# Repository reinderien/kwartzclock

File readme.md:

This is the code associated with the
[KwartzLab electronics demo event](https://gist.github.com/reinderien/ab7dbbdbca7b7f1a77dfda12d686f1ef).

Also see the
[bill of materials](https://docs.google.com/spreadsheets/d/1yXx0iprRUhsX16thSTnNfLWV875vi7FYF72Nl2V39cM/edit?usp=sharing).

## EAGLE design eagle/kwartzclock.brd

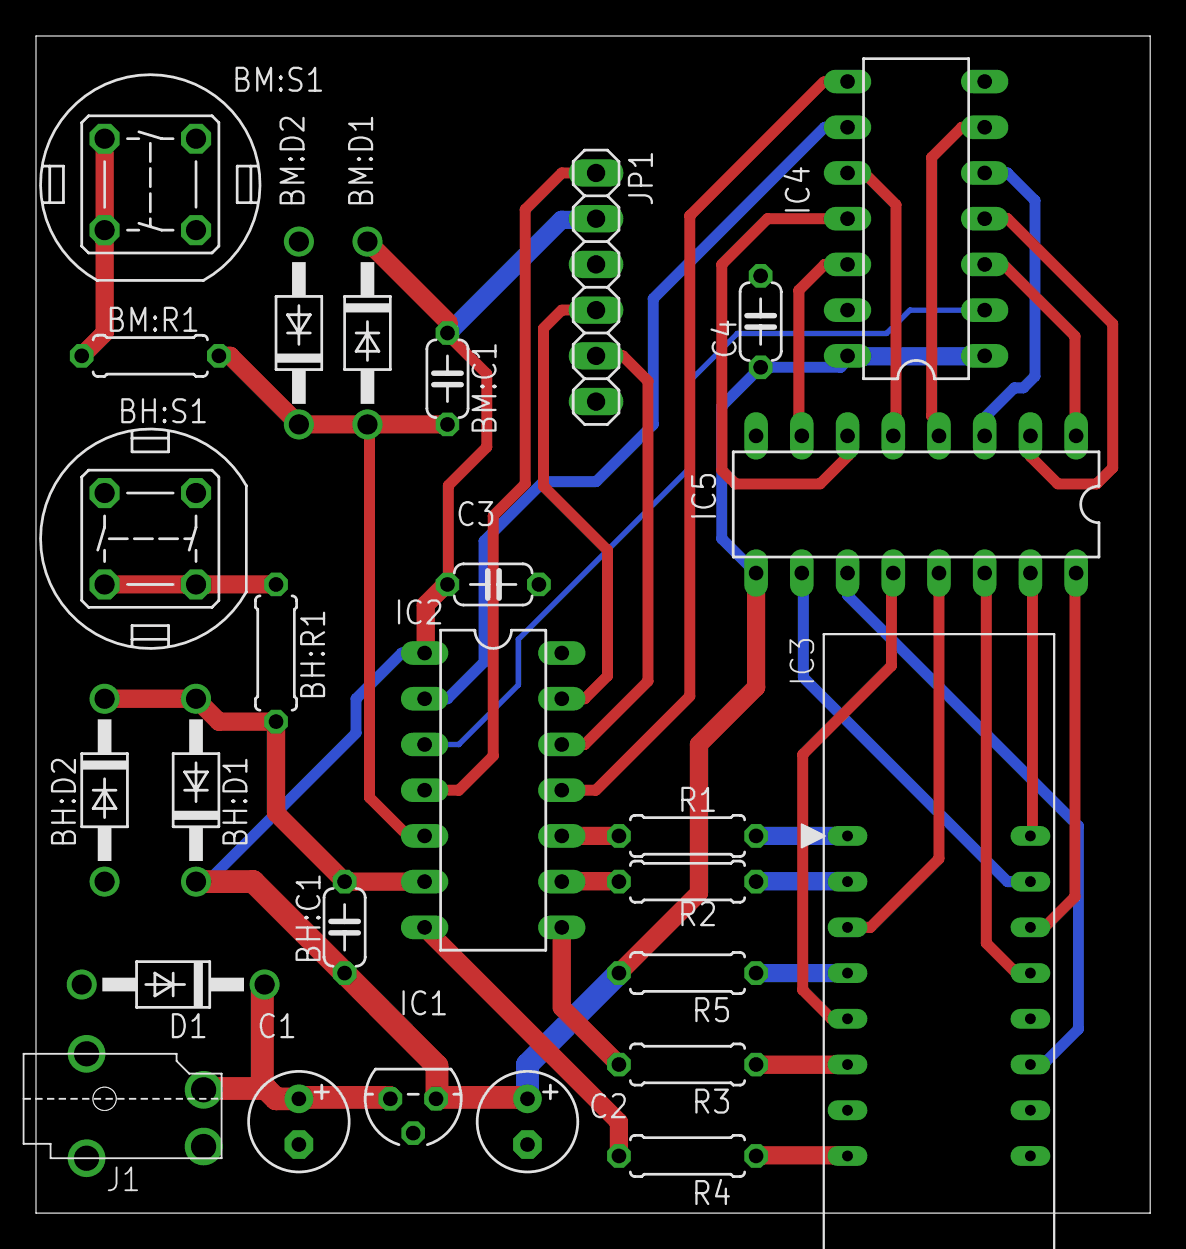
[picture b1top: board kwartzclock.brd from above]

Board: 2 copper layers, 61.9 x 65.4 mm, 27 parts (0 on the bottom side), 36 nets.

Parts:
BH:C1: 330nF; C050-024X044
BH:D1, BH:D2: SB160; DO41-10
BH:R1: 470R; 0207/7
BH:S1: TR1-01; DTE6
BM:C1: 330nF; C050-024X044
BM:D1, BM:D2: SB160; DO41-10
BM:R1: 470R; 0207/7
BM:S1: TR1-01; DTE6
C1, C2: 10uF; E2,5-6
C3, C4: 2.2uF; C050-024X044
D1: SB160; DO41-10
IC1: L78L33ACZ; TO92
IC2: PIC18(L)F15323-I/P; DIL14
IC3: TGCG1050M; DIP16-WIDE
IC4: 74HC164N; DIL14
IC5: ULN2003AN; DIL16
J1: PJ-071
JP1: PH1-06-UA; 1X06
R1, R2, R3, R4: 91R; 0207/7
R5: 330R; 0207/7

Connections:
!CLR: IC2.2, IC4.9
!DRVA: IC3.14, IC5.16
!DRVB: IC3.16, IC5.15
!DRVC: IC3.13, IC5.14
!DRVD: IC3.3, IC5.13
!DRVE: IC3.5, IC5.12
!DRVF: IC3.11, IC5.11
!DRVG: IC3.15, IC5.10
!HBUT: BH:C1.2, BH:D1.A, BH:D2.C, BH:R1.2, IC2.6
!MBUT: BM:C1.2, BM:D1.A, BM:D2.C, BM:R1.2, IC2.5
!MCLR: IC2.4, JP1.1
+3V3: BH:C1.1, BH:D1.C, BM:C1.1, BM:D1.C, C2.+, C3.1, C4.1, IC1.1, IC2.1, IC4.1, IC4.14, IC5.9, JP1.2, R5.2
BH:!BUT_IN: BH:R1.1, BH:S1.1, BH:S1.2
BM:!BUT_IN: BM:R1.1, BM:S1.1, BM:S1.2
CLK: IC2.11, IC4.8
D1: IC2.10, R1.2
D1LIM: IC3.1, R1.1
D2: IC2.9, R2.2
D2LIM: IC3.2, R2.1
D3: IC2.8, R3.2
D3LIM: IC3.6, R3.1
D4: IC2.7, R4.2
D4LIM: IC3.8, R4.1
DAT: IC2.3, IC4.2
GND: BH:D2.A, BH:S1.3, BH:S1.4, BM:D2.A, BM:S1.3, BM:S1.4, C1.-, C2.-, C3.2, C4.2, D1.A, IC1.2, IC2.14, IC3.12, IC4.7, IC5.8, J1.2, J1.3, J1.4, JP1.3
L12LIM: IC3.4, R5.1
PGC: IC2.12, JP1.5
PGD: IC2.13, JP1.4
SRA: IC4.3, IC5.1
SRB: IC4.4, IC5.2
SRC: IC4.5, IC5.3
SRD: IC4.6, IC5.4
SRE: IC4.10, IC5.5
SRF: IC4.11, IC5.6
SRG: IC4.12, IC5.7
V+: C1.+, D1.C, IC1.3, J1.1

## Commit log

2020-02-13 Add readme; update clock for low frequency source
2020-03-10 Fix strobe order
2020-03-11 Use fosc/4, for some reason fosc looks to be 8MHz
2020-03-14 Updated for consistent fosc
2020-03-14 Fix erroneous reference to MFINTOSC; pretty printing
2020-03-14 Add button filter simulation
